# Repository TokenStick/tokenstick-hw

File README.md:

# tokenstick-hw

Hardware design files for TokenStick, a USB-attached accelerator for running LLMs locally.

**Status: early design. Nothing here has been built or tested yet.** The schematic is partial, there is no PCB layout, and several values are placeholders. Do not fabricate from this repository.

## What the board is

- **Accelerator:** Rockchip RK1828 AI co-processor (20 TOPS, 5 GB in-package DRAM, FCBGA-746)
- **Data:** USB-C, USB 3.0 device (5 Gbps), with a SuperSpeed mux for cable flip
- **Power:** a second USB-C port with USB Power Delivery (9-20 V), stepped down on board
- **Form:** USB stick with an aluminum enclosure used as the heatsink

```
 USB-C DATA ──► ESD ──► HD3SS3220 (CC + SS mux) ──► RK1828
                                                      ▲
 USB-C PWR ──► STUSB4500 (PD sink) ──► P-FET ──► VIN ──► 5V buck ──► core / DRAM rails (not designed yet)
```

## Repository layout

| Path | Contents |
|---|---|
| `kicad/lib/` | KiCad symbol and footprint for RK1820/RK1828, the parsed pin list, and the generator script |
| `docs/design-notes.md` | Design decisions, datasheet findings, block descriptions and open questions |
| `docs/bom-draft.csv` | Parts placed in the schematic so far |
| `assets/` | Logo files |

## Design progress

- [x] Chip selection and architecture
- [x] RK1828 symbol and footprint (746 balls, generated from the datasheet pin list)
- [x] Schematic: USB-C data input, ESD, SuperSpeed mux
- [x] Schematic: USB PD power input
- [x] Schematic: 5 V buck
- [x] Schematic: RK1828 USB connections and boot strap
- [ ] Schematic: core (0.9 V), DRAM and analog power rails
- [ ] Schematic: clock, reset, power control, unused pins
- [ ] PCB layout
- [ ] Prototype and bring-up

The schematic is currently drawn in Cherry Blossom (a browser-based editor) and has not been exported to this repository yet.

## Known gaps

These are blocking items, not polish:

- **Power rails for the RK1828 are not designed.** The public datasheet gives voltages but no current figures and no power sequencing. This needs the Rockchip hardware design guide.
- **Power budget is unresolved.** A third-party RK1828 module lists 13.6 W average and 29.4 W peak. The 5 V buck (6 A) and the stick-sized enclosure have not been validated against that.
- **Peripheral circuits are checked on paper only.** The STUSB4500, HD3SS3220 and TPS56637 circuits were compared with the manufacturers' datasheets (see `docs/design-notes.md`, section 7), not tested.
- **Placeholders:** the inductor part and footprint, the 24 MHz crystal, and the VBUS detect divider.
- **STUSB4500 needs NVM programming.** The settings are in `docs/stusb4500-nvm.md`; the profile currents wait for the power budget. I2C is on test points.
- **The RK1828 land pattern is unverified.** Pad diameter (0.30 mm) is a starting value, not a fab-validated pattern.
- **Chip availability.** It is not confirmed that Rockchip sells the RK1828 as a bare chip rather than only as a module.

See `docs/design-notes.md` for details.

## License

Copyright TokenStick contributors 2026.

This source describes Open Hardware and is licensed under the CERN-OHL-S v2.

You may redistribute and modify this source and make products using it under the terms of the CERN-OHL-S v2 (see `LICENSE`, or https://ohwr.org/cern_ohl_s_v2.txt).

This source is distributed WITHOUT ANY EXPRESS OR IMPLIED WARRANTY, INCLUDING OF MERCHANTABILITY, SATISFACTORY QUALITY AND FITNESS FOR A PARTICULAR PURPOSE. Please see the CERN-OHL-S v2 for applicable conditions.

Source location: https://github.com/TokenStick/tokenstick-hw

As per CERN-OHL-S v2 section 4, should you produce hardware based on this source, you must where practicable maintain the Source Location visible on the external case of the product or other products you make using this source.

The TokenStick name and logo in `assets/` are not covered by this licence.

Rockchip, RK1820 and RK1828 are trademarks of their owner. This project is not affiliated with Rockchip.

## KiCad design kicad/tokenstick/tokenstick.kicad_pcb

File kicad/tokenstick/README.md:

# TokenStick KiCad board

Both files of the KiCad 7 project are generated:

- `build_board.py` holds the netlist, the placement and the hand-defined USB routes and writes `tokenstick.kicad_pcb`
- `build_schematic.py` reads the same netlist and writes `tokenstick.kicad_sch` and `../lib/TokenStick_Parts.kicad_sym`

```
python3 build_board.py       # needs the pcbnew module and the KiCad footprint libraries
python3 build_schematic.py   # needs the KiCad symbol libraries
kicad-cli sch export netlist tokenstick.kicad_sch -o /tmp/ts.net && python3 check_netlist.py /tmp/ts.net
python3 drc.py unconnected_items lib_footprint_issues
python3 impedance_fd.py      # field solver for the USB pair geometry, takes a few minutes
```

State:

- 6 layers: F.Cu signal, In1 GND, In2 signal, In3 one VBUS link at J1, In4 GND, B.Cu signal
- Routed by hand (in `build_board.py`): USB-C data connector to the ESD arrays, the HD3SS3220 mux, the AC coupling capacitors and the RK1828 SuperSpeed balls; USB 2.0 D+/D- on In2; CC1/CC2 on the bottom layer
- Routed by `autoroute.py`, a small grid maze router: USB PD input, FET switch, 5 V buck, 3.3 V regulator, mux support parts and a ground via for every SMD ground pad. Copper areas for VBUS, VIN, the switch node and 5 V are defined as rectangles in `build_board.py`
- Not routed: everything on the RK1828 except USB (365 ground balls, all supply rails)
- The schematic is drawn in five framed blocks (USB data path, PD input, 5 V buck, RK1828, test points). Passives sit next to the IC pin they belong to and are wired to it; other connections use net labels. `check_netlist.py` compares the netlist exported from the schematic with the board netlist by connectivity
- Board footprints are not linked to the schematic symbols by UUID. If you use "Update PCB from Schematic", tick "Re-link footprints to schematic symbols based on their reference designators"

See `docs/design-notes.md`, section 9, for the routing decisions and the open review items.

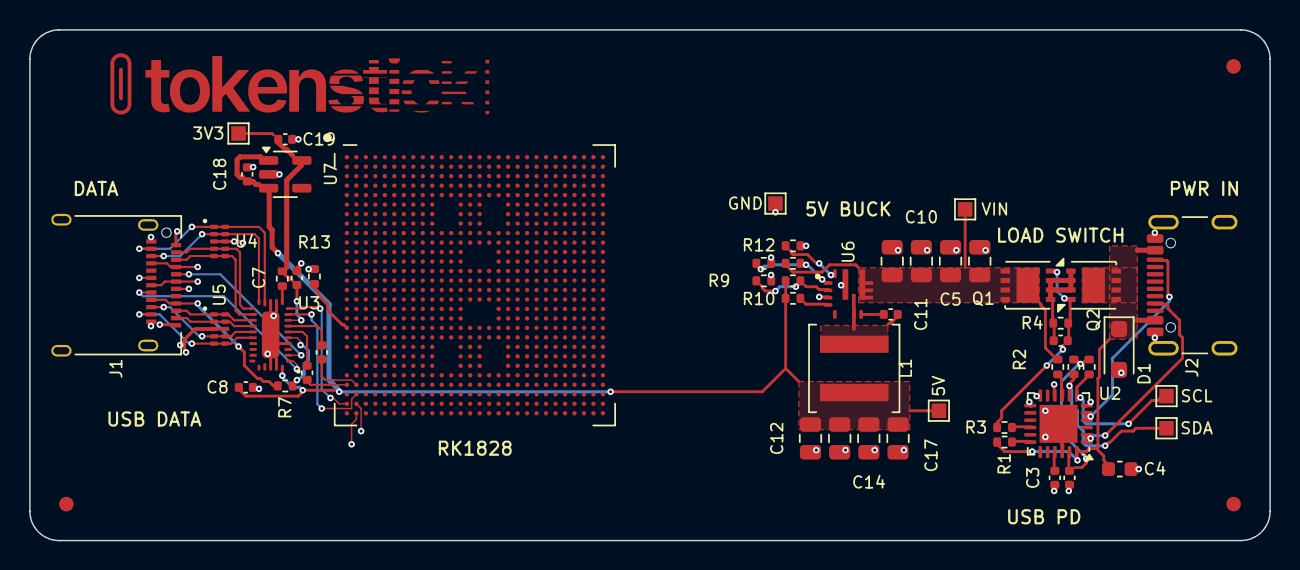
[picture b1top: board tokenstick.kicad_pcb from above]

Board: 6 copper layers, 85.0 x 35.0 mm, 57 parts (0 on the bottom side), 44 nets.

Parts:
C1, C7, C8, C11, C15, C16: 100nF; C_0402_1005Metric
C2, C3, C18, C19: 1uF; C_0402_1005Metric
C4: 1uF 50V; C_0603_1608Metric
C5, C6, C9, C10: 10uF 35V; C_0805_2012Metric
C12, C13, C14, C17: 22uF; C_0805_2012Metric
D1: SMF24A; D_SOD-123F
FID1, FID2, FID3: Fiducial; Fiducial_1mm_Mask2mm
J1: 12401610E4#2A; USB_C_Receptacle_Amphenol_12401610E4-2A
J2: USB4105-GF-A; USB_C_Receptacle_GCT_USB4105-xx-A_16P_TopMnt_Horizontal
L1: 3.3uH; L_Coilcraft_XAL5030-XXX
LG1: logotype; TokenStick_Logotype
Q1, Q2: AON7403; DFN-8-1EP_3x3mm_P0.65mm_EP1.55x2.4mm
R1: 470; R_0402_1005Metric
R2: 1k; R_0402_1005Metric
R3: 22k; R_0402_1005Metric
R4, R10: 100k; R_0402_1005Metric
R5, R6, R9, R12: 10k; R_0402_1005Metric
R7: 900k; R_0402_1005Metric
R8: 73.2k; R_0402_1005Metric
R11: 169k; R_0402_1005Metric
R13: 0R; R_0402_1005Metric
R14: 36.1k; R_0402_1005Metric
R15: 200k; R_0402_1005Metric
TP1: VIN; TestPoint_Pad_1.0x1.0mm
TP2: 5V; TestPoint_Pad_1.0x1.0mm
TP3: 3V3; TestPoint_Pad_1.0x1.0mm
TP4: GND; TestPoint_Pad_1.0x1.0mm
TP5: SCL; TestPoint_Pad_1.0x1.0mm
TP6: SDA; TestPoint_Pad_1.0x1.0mm
U1: RK1828; Rockchip_RK182X_FCBGA-746_19.0x19.0mm_Layout28x28_P0.65mm
U2: STUSB4500QTR; QFN-24-1EP_4x4mm_P0.5mm_EP2.6x2.6mm
U3: HD3SS3220RNH; Texas_RNH0030A_WQFN-30-1EP_2.5x4.5mm_P0.4mm_EP1.2x3.2mm
U4, U5: TPD4E05U06DQA; USON-10_2.5x1.0mm_P0.5mm
U6: TPS56637RPA; Texas_RPA0010A_VQFN-HR-10_3x3mm
U7: AP2112K-3.3; SOT-23-5

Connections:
3V3: C7.1, C19.1, R15.2, TP3.1, U3.8, U7.5
5V: C8.1, C12.1, C13.1, C14.1, C17.1, C18.1, L1.2, R8.1, R10.1, TP2.1, U3.30, U7.1, U7.3
5V_PG: R10.2, U6.4
BUCK_EN: R11.2, R14.1, U6.1
BUCK_FB: R8.2, R9.1, U6.2
BUCK_SW: C11.2, L1.1, U6.6
C_RX1_N: J1.B10, U3.15, U4.2, U4.9
C_RX1_P: J1.B11, U3.14, U4.1, U4.10
C_RX2_N: J1.A10, U3.18, U5.1, U5.10
C_RX2_P: J1.A11, U3.19, U5.2, U5.9
C_TX1_N: J1.A3, U3.17, U4.5, U4.6
C_TX1_P: J1.A2, U3.16, U4.4, U4.7
C_TX2_N: J1.B3, U3.20, U5.4, U5.7
C_TX2_P: J1.B2, U3.21, U5.5, U5.6
DATA_CC1: J1.A5, U3.2
DATA_CC2: J1.B5, U3.1
GND: C2.2, C3.2, C4.2, C5.2, C6.2, C7.2, C8.2, C9.2, C10.2, C12.2, C13.2, C14.2, C17.2, C18.2, C19.2, D1.2, J1.A1, J1.A12, J1.B1, J1.B12, J1.S1, J2.A1, J2.A12, J2.B1, J2.B12, J2.S1, R9.2, R12.2, R13.2, R14.2, TP4.1, U1.A1, U1.A5, U1.A7, U1.A9, U1.A11, U1.A13, U1.A16, U1.A18, U1.A20, U1.A23, U1.A25, U1.A27, U1.A28, U1.AA3, U1.AA5, U1.AA7, U1.AA8, U1.AA9, U1.AA13, U1.AA15, U1.AA19, U1.AA21, U1.AA22, U1.AA23, U1.AA24, U1.AA25, U1.AA26, U1.AA27, U1.AA28, U1.AB2, U1.AB3, U1.AB5, U1.AB8, U1.AB9, U1.AB13, U1.AB14, U1.AB15, U1.AB19, U1.AC4, U1.AC6, U1.AC7, U1.AC9, U1.AC13, U1.AC19, U1.AC21, U1.AC22, U1.AC23, U1.AC24, U1.AC25, U1.AC26, U1.AC27, U1.AC28, U1.AD3, U1.AD5, U1.AD6, U1.AD9, U1.AD12, U1.AD13, U1.AD16, U1.AD19, U1.AE3, U1.AE5, U1.AE7, U1.AE9, U1.AE11, U1.AE13, U1.AE16, U1.AE19, U1.AE20, U1.AE22, U1.AE24, U1.AE26, U1.AE28, U1.AF1, U1.AF3, U1.AF5, U1.AF7, U1.AF9, U1.AF11, U1.AF13, U1.AF16, U1.AF18, U1.AF20, U1.AF21, U1.AF23, U1.AF25, U1.AF27, U1.AG4, U1.AG5, U1.AG7, U1.AG9, U1.AG11, U1.AG13, U1.AG16, U1.AG18, U1.AG20, U1.AG22, U1.AG24, U1.AG26, U1.AG28, U1.AH1, U1.AH4, U1.AH5, U1.AH7, U1.AH9, U1.AH11, U1.AH13, U1.AH16, U1.AH18, U1.AH20, U1.AH21, U1.AH23, U1.AH25, U1.AH27, U1.AH28, U1.B5, U1.B7, U1.B9, U1.B11, U1.B13, U1.B16, U1.B18, U1.B20, U1.B22, U1.B24, U1.B26, U1.B28, U1.C5, U1.C7, U1.C9, U1.C11, U1.C13, U1.C16, U1.C18, U1.C20, U1.C21, U1.C23, U1.C25, U1.C27, U1.D5, U1.D7, U1.D9, U1.D11, U1.D13, U1.D16, U1.D19, U1.D20, U1.D22, U1.D24, U1.D26, U1.D28, U1.E5, U1.E6, U1.E9, U1.E12, U1.E13, U1.E16, U1.E19, U1.F3, U1.F5, U1.F6, U1.F9, U1.F13, U1.F19, U1.F21, U1.F22, U1.F23, U1.F24, U1.F25, U1.F26, U1.F27, U1.F28, U1.G5, U1.G6, U1.G7, U1.G9, U1.G13, U1.G14, U1.G15, U1.G19, U1.H1, U1.H3, U1.H6, U1.H7, U1.H8, U1.H9, U1.H13, U1.H15, U1.H19, U1.H21, U1.H22, U1.H23, U1.H24, U1.H25, U1.H26, U1.H27, U1.H28, U1.J4, U1.J5, U1.J6, U1.J7, U1.J8, U1.J9, U1.J13, U1.J15, U1.J19, U1.K3, U1.K5, U1.K6, U1.K8, U1.K9, U1.K10, U1.K11, U1.K12, U1.K13, U1.K16, U1.K17, U1.K18, U1.K19, U1.K20, U1.K21, U1.K22, U1.K23, U1.K24, U1.K25, U1.K26, U1.K27, U1.K28, U1.L5, U1.L6, U1.L9, U1.L13, U1.L17, U1.M5, U1.M6, U1.M7, U1.M8, U1.M9, U1.M10, U1.M11, U1.M12, U1.M13, U1.M17, U1.M18, U1.M19, U1.M20, U1.M21, U1.M22, U1.M23, U1.M24, U1.M25, U1.M26, U1.M27, U1.M28, U1.N3, U1.N5, U1.N6, U1.N8, U1.N10, U1.N14, U1.N15, U1.N16, U1.P4, U1.P6, U1.P8, U1.P10, U1.P11, U1.P12, U1.P13, U1.P17, U1.P18, U1.P20, U1.P21, U1.P22, U1.P23, U1.P24, U1.P25, U1.P26, U1.P27, U1.P28, U1.R5, U1.R6, U1.R7, U1.R8, U1.R10, U1.R11, U1.R12, U1.R13, U1.R14, U1.R15, U1.R16, U1.R17, U1.R18, U1.R19, U1.R20, U1.R21, U1.R22, U1.R23, U1.R24, U1.R25, U1.R26, U1.R27, U1.R28, U1.T4, U1.T5, U1.T6, U1.T7, U1.T8, U1.T10, U1.T14, U1.T15, U1.T16, U1.U5, U1.U9, U1.U10, U1.U11, U1.U12, U1.U13, U1.U17, U1.U18, U1.U19, U1.U20, U1.U21, U1.U22, U1.U23, U1.U24, U1.U25, U1.U26, U1.U27, U1.U28, U1.V5, U1.V9, U1.V13, U1.V17, U1.W3, U1.W5, U1.W6, U1.W9, U1.W10, U1.W11, U1.W12, U1.W13, U1.W16, U1.W17, U1.W18, U1.W19, U1.W20, U1.W21, U1.W22, U1.W23, U1.W24, U1.W25, U1.W26, U1.W27, U1.W28, U1.Y1, U1.Y2, U1.Y3, U1.Y4, U1.Y5, U1.Y6, U1.Y9, U1.Y13, U1.Y15, U1.Y19, U2.6, U2.10, U2.12, U2.13, U2.22, U2.25, U3.4, U3.12, U3.13, U3.28, U3.29, U3.31, U4.3, U4.8, U5.3, U5.8, U6.3, U6.9, U7.2
unnamed: C11.1, U6.7
unnamed: C15.1, U1.AE1
unnamed: C16.1, U1.AE2
unnamed: R1.2, U2.18
unnamed: R2.2, U2.9
unnamed: R3.2, U2.16
unnamed: R7.2, U3.5
unnamed: R12.1, U6.10
unnamed: R13.1, U1.W1
PD_CC1: J2.A5, U2.1, U2.2
PD_CC2: J2.B5, U2.4, U2.5
PD_GATE: C1.2, Q1.4, Q2.4, R3.1, R4.2
PD_SCL: R6.2, TP5.1, U2.7
PD_SDA: R5.2, TP6.1, U2.8
PD_SRC: C1.1, Q1.1, Q1.2, Q1.3, Q2.1, Q2.2, Q2.3, R4.1
U2_VREG_1V2: C3.1, U2.21
USB_DIR: R15.1, U3.11
USB_DM: J1.A7, J1.B7, U1.AH2
USB_DP: J1.A6, J1.B6, U1.AG2
USB_SSRX_N: U1.AG1, U3.10
USB_SSRX_P: U1.AF2, U3.9
USB_SSTX_N: C16.2, U3.7
USB_SSTX_P: C15.2, U3.6
VBUS_DATA: J1.A4, J1.A9, J1.B4, J1.B9, R7.1
VBUS_PD: C4.1, D1.1, J2.A4, J2.A9, J2.B4, J2.B9, Q2.5, Q2.6, Q2.7, Q2.8, Q2.9, R1.1, U2.24
VIN: C5.1, C6.1, C9.1, C10.1, Q1.5, Q1.6, Q1.7, Q1.8, Q1.9, R2.1, R11.1, TP1.1, U6.8
VREG_2V7: C2.1, R5.1, R6.1, U2.23

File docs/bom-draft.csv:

Ref,Block,Part,Value,Package,Status,Notes
U1,RK1828,RK1828,,FCBGA-746,Unverified land,Symbol and footprint generated from datasheet pin list
C15-C16,RK1828,Capacitor,100nF,0402,OK,SuperSpeed TX AC coupling
R13,RK1828,Resistor,0R,0402,To confirm,Boot strap on SARADC_IN0_BOOT
J1,USB-C DATA,Amphenol 12401610E4#2A (LCSC C5119948),,SMD (shell THT),OK,24-pin USB-C receptacle
U3,USB-C DATA,HD3SS3220RNHR,,QFN-30,Checked vs datasheet,CC controller and SuperSpeed mux; UFP and GPIO mode
U4-U5,USB-C DATA,TPD4E05U06DQAR,,USON-10,OK,ESD on SuperSpeed pairs
R7,USB-C DATA,Resistor,900k,0402,Checked vs datasheet,VBUS_DET series resistor
R15,USB-C DATA,Resistor,200k,0402,Checked vs datasheet,DIR pull-up to 3V3 (required)
C7-C8,USB-C DATA,Capacitor,100nF,0402,OK,Decoupling
J2,PD POWER INPUT,USB4105-GF-A,,SMD,OK,16-pin USB-C receptacle (power only)
U2,PD POWER INPUT,STUSB4500QTR,,QFN-24,Checked vs datasheet,USB PD sink controller; NVM must be programmed
Q1-Q2,PD POWER INPUT,AON7403,,DFN-8 3x3,Checked vs datasheet,Back-to-back P-channel 30V VBUS switch (as in ST reference)
D1,PD POWER INPUT,SMF24A,,SOD-123F,OK,VBUS TVS
R1,PD POWER INPUT,Resistor,470,0402,Checked vs datasheet,VBUS_VS_DISCH
R2,PD POWER INPUT,Resistor,1k,0402,Checked vs datasheet,DISCH
R3,PD POWER INPUT,Resistor,22k,0402,Checked vs datasheet,Gate drive
R4,PD POWER INPUT,Resistor,100k,0402,Checked vs datasheet,Gate to common source
R5-R6,PD POWER INPUT,Resistor,10k,0402,OK,I2C pull-ups (R5 SDA; R6 SCL)
C1,PD POWER INPUT,Capacitor,100nF,0402,Checked vs datasheet,Gate soft-start
C2-C3,PD POWER INPUT,Capacitor,1uF,0402,OK,VREG_2V7 and VREG_1V2
C4,PD POWER INPUT,Capacitor,1uF 50V,0603,OK,VBUS
C5-C6,PD POWER INPUT,Capacitor,10uF 35V,0805,OK,VIN bulk
U6,5V BUCK,TPS56637RPAR,,VQFN-10,Checked vs datasheet,6A buck; values from TI 5V reference design
L1,5V BUCK,Inductor,3.3uH,Placeholder footprint,Value per TI table; needs a real 6A+ power inductor
C9-C10,5V BUCK,Capacitor,10uF 35V,0805,OK,Input
C11,5V BUCK,Capacitor,100nF,0402,OK,Bootstrap
C12-C14 C17,5V BUCK,Capacitor,22uF 10V,0805,Checked vs datasheet,Output (4 x 22uF)
R8,5V BUCK,Resistor,73.2k,0402,Checked vs datasheet,Feedback top
R9,5V BUCK,Resistor,10k,0402,Checked vs datasheet,Feedback bottom
R10,5V BUCK,Resistor,100k,0402,OK,Power-good pull-up
R11,5V BUCK,Resistor,169k,0402,Checked vs datasheet,EN divider top
R14,5V BUCK,Resistor,36.1k,0402,Checked vs datasheet,EN divider bottom
R12,5V BUCK,Resistor,10k,0402,Checked vs datasheet,MODE to GND selects Eco-mode; leave open for FCCM
TP1-TP6,TEST,Test point (no part),,1 mm pad,OK,VIN 5V 3V3 GND SCL SDA; SCL and SDA program the STUSB4500 NVM
FID1-FID3,TEST,Fiducial (no part),,1 mm copper,OK,Three corners
